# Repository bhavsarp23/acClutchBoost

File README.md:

# AC Clutch Boost Circuit

acClutchBoost is a KiCad hardware project designed to improve AC clutch engagement on the **8th Generation Honda Civic Si**. The project addresses a common issue where the AC clutch fails to engage reliably due to increased air gap from clutch wear, particularly at high ambient temperatures.

The repository includes the **schematic**, **PCB layout**, and **BOM** required to build the circuit.

---

## Background

Over time, wear in the AC clutch friction material increases the air gap between the clutch plate and pulley. As the gap grows, the clutch solenoid may no longer generate sufficient magnetic force to pull in the clutch, especially under adverse conditions such as high temperatures.

At elevated temperatures, clutch engagement can degrade further, potentially due to reduced magnetic permeability of the ferrous components or increased coil resistance. The result is intermittent or complete AC failure despite correct ECU commands.

---

## Concept

When the vehicle ECU commands AC clutch engagement, **acClutchBoost** briefly increases the voltage supplied to the clutch coil above the nominal automotive range (approximately 12–14 V). This higher voltage is applied for a short, configurable duration to ensure reliable pull-in of the clutch. After this initial boost period, the circuit returns the clutch supply to normal voltage to avoid overheating or long-term stress.

This approach improves engagement reliability without permanent mechanical modification of the clutch assembly.

---

## Key Features

- Interfaces directly with the factory AC clutch control signal
- Momentary voltage boost during clutch engagement
- Adjustable boost voltage
- Adjustable boost duration
- Returns to nominal voltage after engagement
- Designed specifically for 8th Gen Civic Si electrical characteristics

---

## Design Overview

The circuit consists of:

- **Non-isolated DC-DC step-up (boost) converter**
  - Trimmable output voltage
  - Raises clutch supply voltage during engagement
- **Relay-based switching**
  - Selects between nominal supply and boosted supply
  - Ensures normal operation after engagement
- **Adjustable timing circuit**
  - Controls the duration of the voltage boost
  - Allows tuning for different wear conditions or temperatures

---

## Repository Contents

- **Schematic**  
  Complete circuit design showing power, control, and timing sections.

- **PCB Layout**  
  Board layout suitable for automotive installation considerations.

- **BOM (Bill of Materials)**  
  Component list with values and part references.

---

## Adjustability

- **Boost Voltage**  
  Set via trim potentiometer on the DC-DC converter.

- **Boost Duration**  
  Controlled by the adjustable timing circuit to apply voltage only during initial engagement. Set via trim potentiometer.

Both parameters can be tuned to balance reliable clutch pull-in with long-term component safety.

---

## Intended Use

This project is intended for:
- Experimental and educational use
- Automotive electronics enthusiasts
- Situations where AC clutch wear causes unreliable engagement

It is not a replacement for proper mechanical repair, but a practical electrical mitigation for a known failure mode.

---

## Tools

- KiCad (for viewing and modifying schematic and PCB)
- Standard PCB fabrication and assembly tools

---

## Disclaimer

This project interfaces with automotive electrical systems. Improper installation or tuning may result in damage to vehicle components or injury. Use at your own risk.

---

## License

## License

This project is licensed under the **CERN Open Hardware Licence v2 – Weakly Reciprocal (CERN-OHL-W v2)**.

You are free to use, modify, manufacture, and distribute this hardware design, provided that any modifications to the licensed material are released under the same license.

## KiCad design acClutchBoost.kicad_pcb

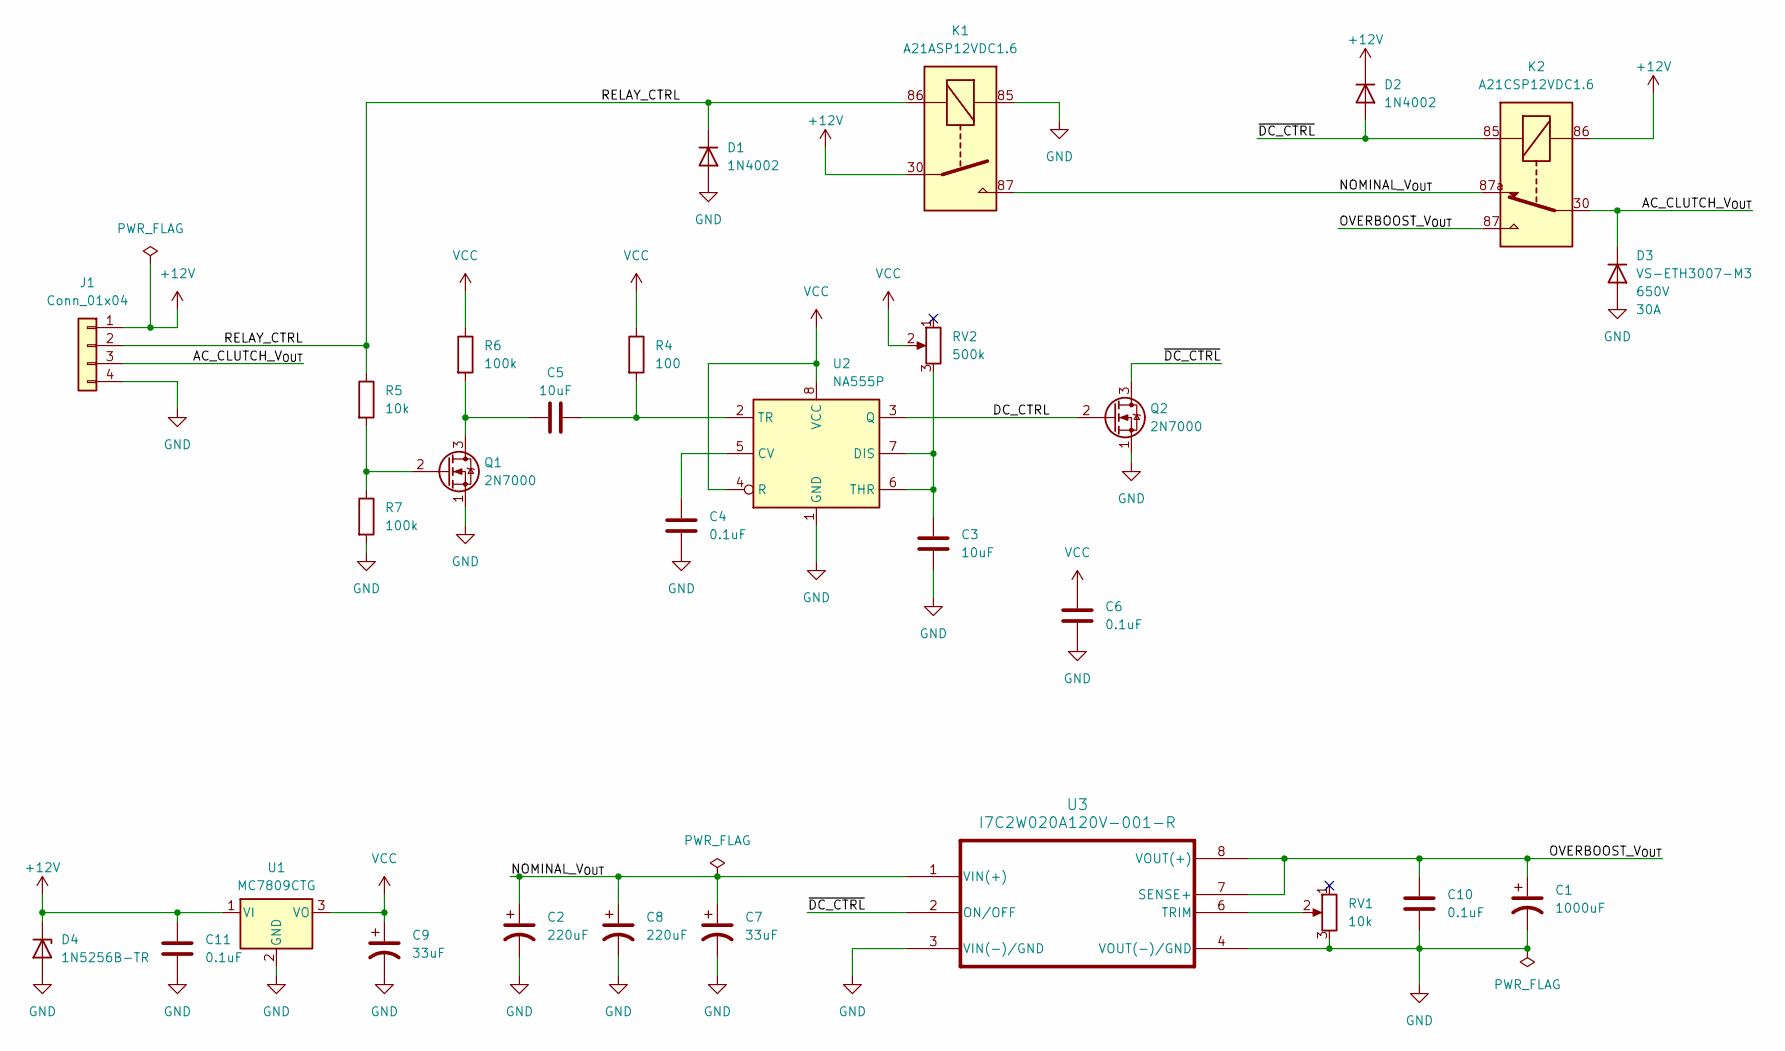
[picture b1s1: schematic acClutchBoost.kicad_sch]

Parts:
C1: 1000uF; CP_Radial_D12.5mm_P5.00mm; PartNumber 35ZLH1000MEFCG412.5X20
C2, C8: 220uF; CP_Radial_D10.0mm_P5.00mm; PartNumber 50ZLH220MEFC10X16
C3, C5: 10uF; C_Disc_D3.8mm_W2.6mm_P2.50mm; PartNumber C324C106K3R5TA
C4, C6, C10, C11: 0.1uF; C_Disc_D3.8mm_W2.6mm_P2.50mm; PartNumber C320C104K5R5TA
C7, C9: 33uF; CP_Radial_D5.0mm_P2.00mm; PartNumber ELE-350ELL330ME11D
D1, D2: 1N4002; D_DO-41_SOD81_P7.62mm_Horizontal; PartNumber 1N4002
D3: VS-ETH3007-M3; TO-220-2_Vertical; Voltage 650V; PartNumber VS-ETH3007-M3
D4: 1N5256B-TR; D_DO-35_SOD27_P7.62mm_Horizontal; PartNumber 1N5256B-TR
J1: Conn_01x04; SolderWire-2.5sqmm_1x04_P7.2mm_D2.4mm_OD3.6mm
K1: A21ASP12VDC1.6; AutomotiveA2Relay_Form1A; PartNumber A21ASP12VDC1.6
K2: A21CSP12VDC1.6; AutomotiveA2Relay_Form1C; PartNumber A21CSP12VDC1.6
Q1, Q2: 2N7000; TO-92_Inline; PartNumber 2N7000
R4: 100; R_Axial_DIN0204_L3.6mm_D1.6mm_P7.62mm_Horizontal
R5: 10k; R_Axial_DIN0204_L3.6mm_D1.6mm_P7.62mm_Horizontal
R6, R7: 100k; R_Axial_DIN0204_L3.6mm_D1.6mm_P7.62mm_Horizontal
RV1: 10k; Potentiometer_Bourns_3296W_Vertical; PartNumber 3296W-1-103LF
RV2: 500k; Potentiometer_Bourns_3296W_Vertical; PartNumber 3296W-1-504LF
U1: MC7809CTG; TO-220-3_Vertical; PartNumber MC7809CTG
U2: NA555P; DIP-8_W7.62mm; PartNumber NA555P
U3: I7C2W020A120V-001-R; CONV_I7C2W020A120V-001-R; PartNumber I7C2W020A120V-001-R

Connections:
+12V: C11.1, D2.1 (K), D4.1 (K), J1.1, K1.30, K2.86, U1.1 (VI)
/AC_CLUTCH_V_{OUT}: D3.1 (K), J1.3, K2.30
/DC_CTRL: Q2.2 (G), U2.3 (Q)
/NOMINAL_V_{OUT}: C2.1, C7.1, C8.1, K1.87, K2.87a, U3.1 (VIN(+))
/OVERBOOST_V_{OUT}: C1.1, C10.1, K2.87, U3.7 (SENSE+), U3.8 (VOUT(+))
/RELAY_CTRL: D1.1 (K), J1.2, K1.86, R5.1
/~DC_CTRL: D2.2 (A), K2.85, Q2.3 (D), U3.2 (ON/OFF)
GND: C1.2, C2.2, C3.2, C4.2, C6.1, C7.2, C8.2, C9.2, C10.2, C11.2, D1.2 (A), D3.2 (A), D4.2 (A), J1.4, K1.85, Q1.1 (S), Q2.1 (S), R7.2, RV1.3, U1.2 (GND), U2.1 (GND), U3.3 (VIN(-)/GND), U3.4 (VOUT(-)/GND)
unnamed: C5.1, Q1.3 (D), R6.2
unnamed: Q1.2 (G), R5.2, R7.1
unnamed: C4.1, U2.5 (CV)
unnamed: C3.1, RV2.3, U2.6 (THR), U2.7 (DIS)
unnamed: C5.2, R4.2, U2.2 (TR)
unnamed: RV1.2, U3.6 (TRIM)
VCC: C6.2, C9.1, R4.1, R6.1, RV2.2, U1.3 (VO), U2.4 (R), U2.8 (VCC)

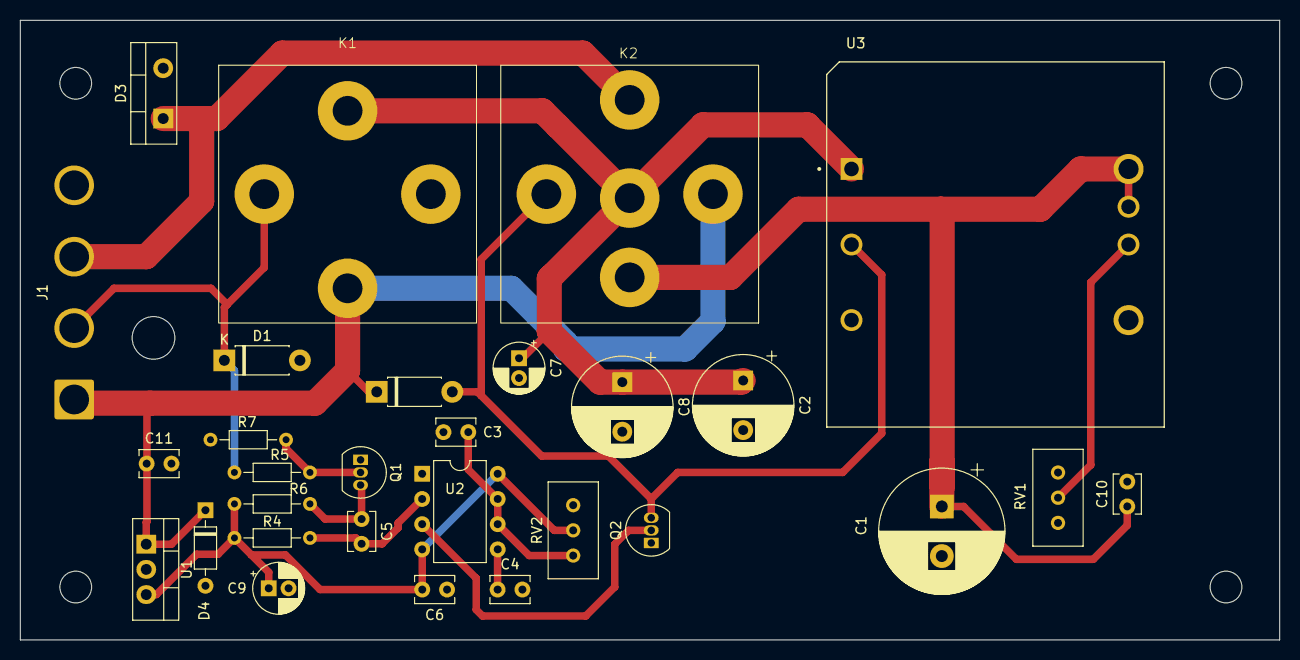
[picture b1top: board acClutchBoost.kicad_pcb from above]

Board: 2 copper layers, 127.0 x 62.5 mm, 29 parts (0 on the bottom side), 15 nets.

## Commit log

2024-07-11 Add files via upload
    Initial commit
2026-01-04 Create README.md for AC Clutch Boost Circuit project
    Add detailed project documentation for acClutchBoost.
2026-01-04 Add CERN Open Hardware Licence Version 2
